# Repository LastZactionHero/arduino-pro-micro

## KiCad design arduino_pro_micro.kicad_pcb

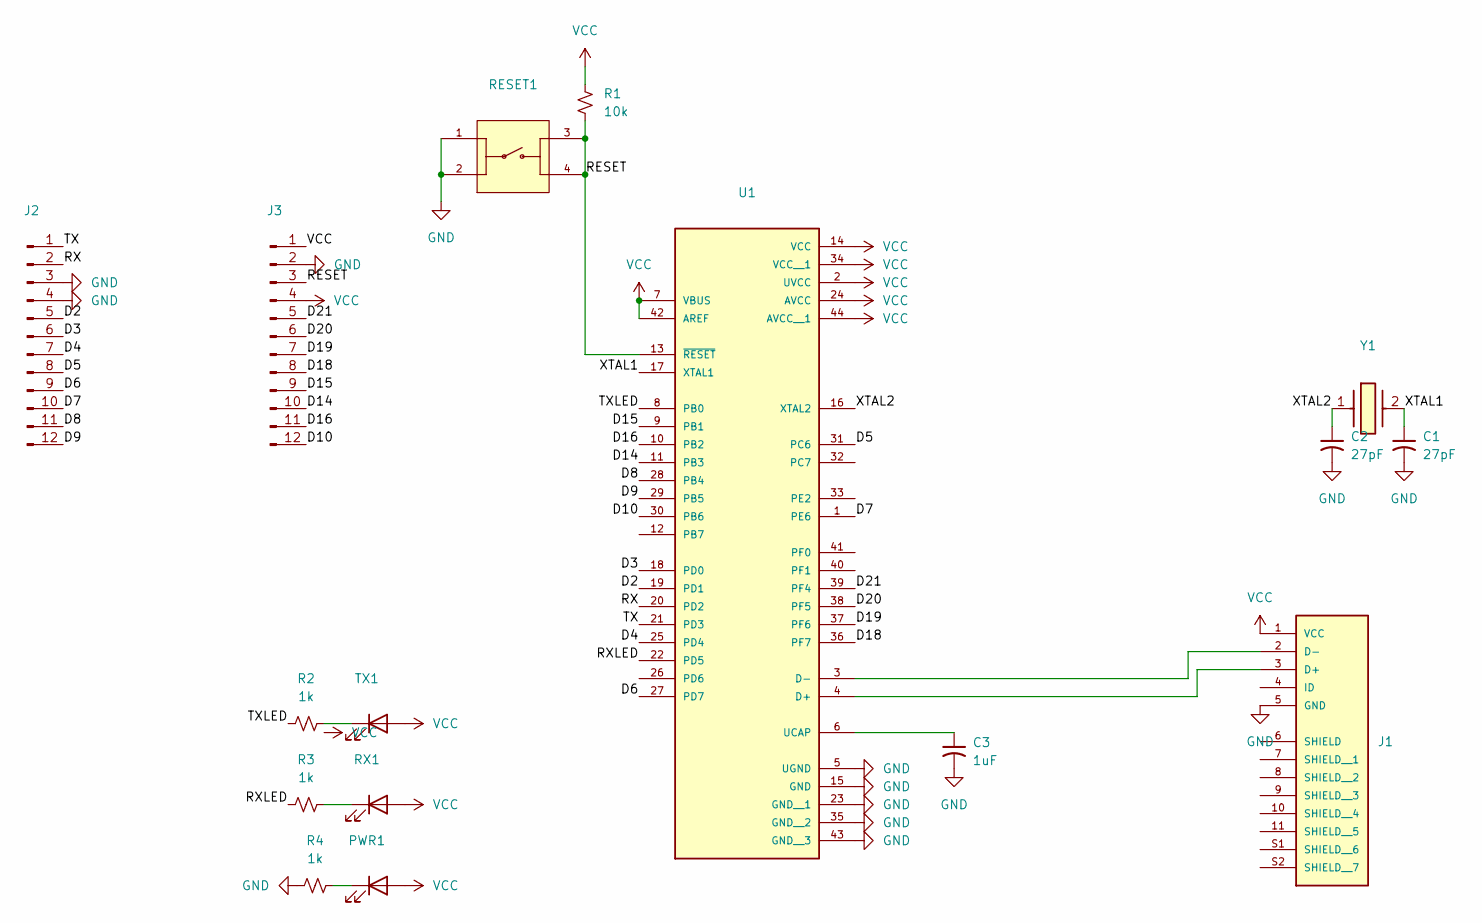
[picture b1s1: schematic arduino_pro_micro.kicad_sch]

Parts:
C1, C2: 27pF; C_0402_1005Metric_Pad0.74x0.62mm_HandSolder
C3: 1uF; C_0402_1005Metric_Pad0.74x0.62mm_HandSolder
J1: 10103594-0001LF; AMPHENOL_10103594-0001LF; PARTREV A
J2, J3: Conn_01x12_Pin; PinHeader_1x12_P2.54mm_Vertical
PWR1: LED; LED_0201_0603Metric_Pad0.64x0.40mm_HandSolder
R1: 10k; R_0402_1005Metric_Pad0.72x0.64mm_HandSolder
R2, R3, R4: 1k; R_0402_1005Metric_Pad0.72x0.64mm_HandSolder
RESET1: 1825910-6; SW_1825910-6-4; PARTREV C10
RX1: LED; LED_0201_0603Metric
TX1: LED; LED_0201_0603Metric
U1: ATMEGA32U4-AU; QFP80P1200X1200X120-44N
Y1: ECS-160-18-5PX-GM-TR; ECS160185PXGMTR; Mouser Part Number 520-160-18-5PX-GM-TR

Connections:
/D2: J2.5, U1.19 (PD1)
/D3: J2.6, U1.18 (PD0)
/D4: J2.7, U1.25 (PD4)
/D5: J2.8, U1.31 (PC6)
/D6: J2.9, U1.27 (PD7)
/D7: J2.10, U1.1 (PE6)
/D8: J2.11, U1.28 (PB4)
/D9: J2.12, U1.29 (PB5)
/D10: J3.12, U1.30 (PB6)
/D14: J3.10, U1.11 (PB3)
/D15: J3.9, U1.9 (PB1)
/D16: J3.11, U1.10 (PB2)
/D18: J3.8, U1.36 (PF7)
/D19: J3.7, U1.37 (PF6)
/D20: J3.6, U1.38 (PF5)
/D21: J3.5, U1.39 (PF4)
/RESET: J3.3, R1.2, RESET1.3, RESET1.4, U1.13 (~RESET)
/RX: J2.2, U1.20 (PD2)
/RXLED: R3.1, U1.22 (PD5)
/TX: J2.1, U1.21 (PD3)
/TXLED: R2.1, U1.8 (PB0)
/XTAL1: C1.1, U1.17 (XTAL1), Y1.2
/XTAL2: C2.1, U1.16 (XTAL2), Y1.1
GND: C1.2, C2.2, C3.2, J1.5 (GND), J2.3, J2.4, J3.2, R4.1, RESET1.1, RESET1.2, U1.5 (UGND), U1.15 (GND), U1.23 (GND__1), U1.35 (GND__2), U1.43 (GND__3)
unnamed: J1.3 (D+), U1.4 (D+)
unnamed: J1.2 (D-), U1.3 (D-)
unnamed: PWR1.1 (K), R4.2
unnamed: R3.2, RX1.1 (K)
unnamed: R2.2, TX1.1 (K)
unnamed: C3.1, U1.6 (UCAP)
VCC: J1.1 (VCC), J3.1, J3.4, PWR1.2 (A), R1.1, RX1.2 (A), TX1.2 (A), U1.2 (UVCC), U1.7 (VBUS), U1.14 (VCC), U1.24 (AVCC), U1.34 (VCC__1), U1.42 (AREF), U1.44 (AVCC__1)

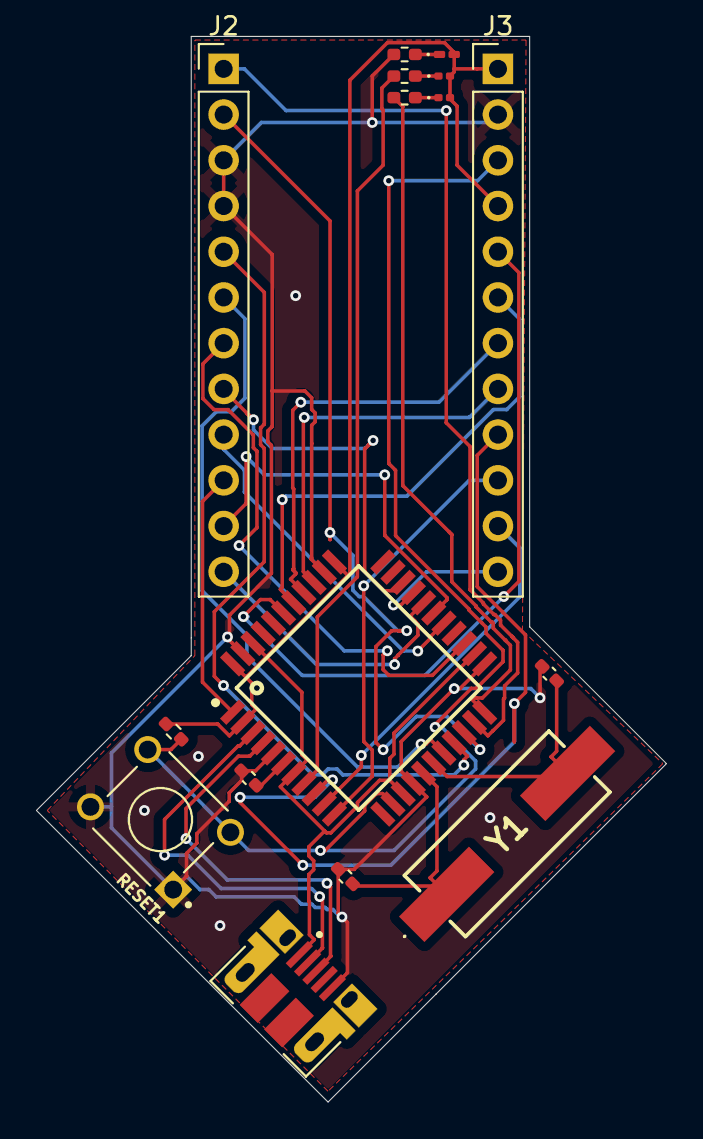
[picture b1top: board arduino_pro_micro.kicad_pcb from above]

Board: 2 copper layers, 35.0 x 59.2 mm, 16 parts (0 on the bottom side), 31 nets.

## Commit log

2025-10-30 PCB and fabrication outputs
